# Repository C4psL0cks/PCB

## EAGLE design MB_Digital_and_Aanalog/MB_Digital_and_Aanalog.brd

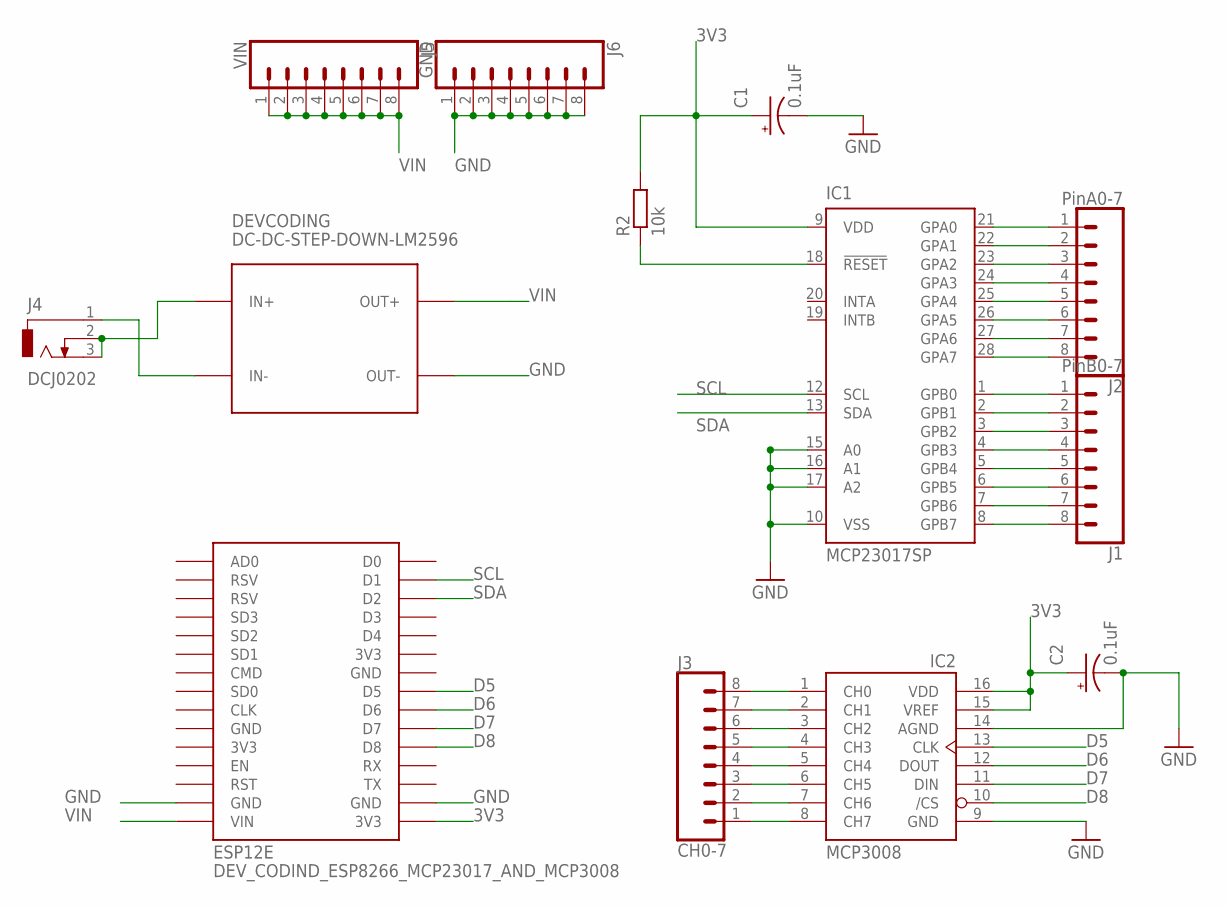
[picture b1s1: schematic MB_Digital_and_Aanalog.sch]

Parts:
C1, C2: 0.1uF; E1,8-4
DEVCODING: DC-DC-STEP-DOWN-LM2596
DEV_CODIND_ESP8266_MCP23017_AND_MCP3008: ESP12E; ESP12E_DEVKIT
IC1: MCP23017SP; DIL28-3
IC2: MCP3008; DIL16
J1: PinB0-7; 1X08_LONGPADS
J2: PinA0-7; 1X08_LONGPADS
J3: CH0-7; 1X08_LONGPADS
J4: DCJ0202
J5: VIN; 1X08_LONGPADS
J6: GND; 1X08_LONGPADS
R2: 10k; 0207/7

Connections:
3V3: C1.+, C2.+, DEV_CODIND_ESP8266_MCP23017_AND_MCP3008.3V3@2 (3V3), IC1.9 (VDD), IC2.15 (VREF), IC2.16 (VDD), R2.2
D5: DEV_CODIND_ESP8266_MCP23017_AND_MCP3008.D5, IC2.13 (CLK)
D6: DEV_CODIND_ESP8266_MCP23017_AND_MCP3008.D6, IC2.12 (DOUT)
D7: DEV_CODIND_ESP8266_MCP23017_AND_MCP3008.D7, IC2.11 (DIN)
D8: DEV_CODIND_ESP8266_MCP23017_AND_MCP3008.D8, IC2.10 (/CS)
GND: C1.-, C2.-, DEVCODING.OUT-, DEV_CODIND_ESP8266_MCP23017_AND_MCP3008.GND@1 (GND), DEV_CODIND_ESP8266_MCP23017_AND_MCP3008.GND@3 (GND), IC1.10 (VSS), IC1.15 (A0), IC1.16 (A1), IC1.17 (A2), IC2.9 (GND), IC2.14 (AGND), J6.1, J6.2, J6.3, J6.4, J6.5, J6.6, J6.7, J6.8
unnamed: IC1.21 (GPA0), J2.1
unnamed: IC1.22 (GPA1), J2.2
unnamed: IC1.23 (GPA2), J2.3
unnamed: IC1.18 (!RESET), R2.1
unnamed: IC1.24 (GPA3), J2.4
unnamed: IC1.25 (GPA4), J2.5
unnamed: IC1.26 (GPA5), J2.6
unnamed: IC1.27 (GPA6), J2.7
unnamed: IC1.28 (GPA7), J2.8
unnamed: IC1.1 (GPB0), J1.1
unnamed: IC1.2 (GPB1), J1.2
unnamed: IC1.3 (GPB2), J1.3
unnamed: IC1.4 (GPB3), J1.4
unnamed: IC1.5 (GPB4), J1.5
unnamed: IC1.6 (GPB5), J1.6
unnamed: IC1.7 (GPB6), J1.7
unnamed: IC1.8 (GPB7), J1.8
unnamed: IC2.1 (CH0), J3.8
unnamed: IC2.2 (CH1), J3.7
unnamed: IC2.3 (CH2), J3.6
unnamed: IC2.4 (CH3), J3.5
unnamed: IC2.5 (CH4), J3.4
unnamed: IC2.6 (CH5), J3.3
unnamed: IC2.7 (CH6), J3.2
unnamed: IC2.8 (CH7), J3.1
unnamed: DEVCODING.IN-, J4.1
unnamed: DEVCODING.IN+, J4.2, J4.3
SCL: DEV_CODIND_ESP8266_MCP23017_AND_MCP3008.D1, IC1.12 (SCL)
SDA: DEV_CODIND_ESP8266_MCP23017_AND_MCP3008.D2, IC1.13 (SDA)
VIN: DEVCODING.OUT+, DEV_CODIND_ESP8266_MCP23017_AND_MCP3008.VIN, J5.1, J5.2, J5.3, J5.4, J5.5, J5.6, J5.7, J5.8

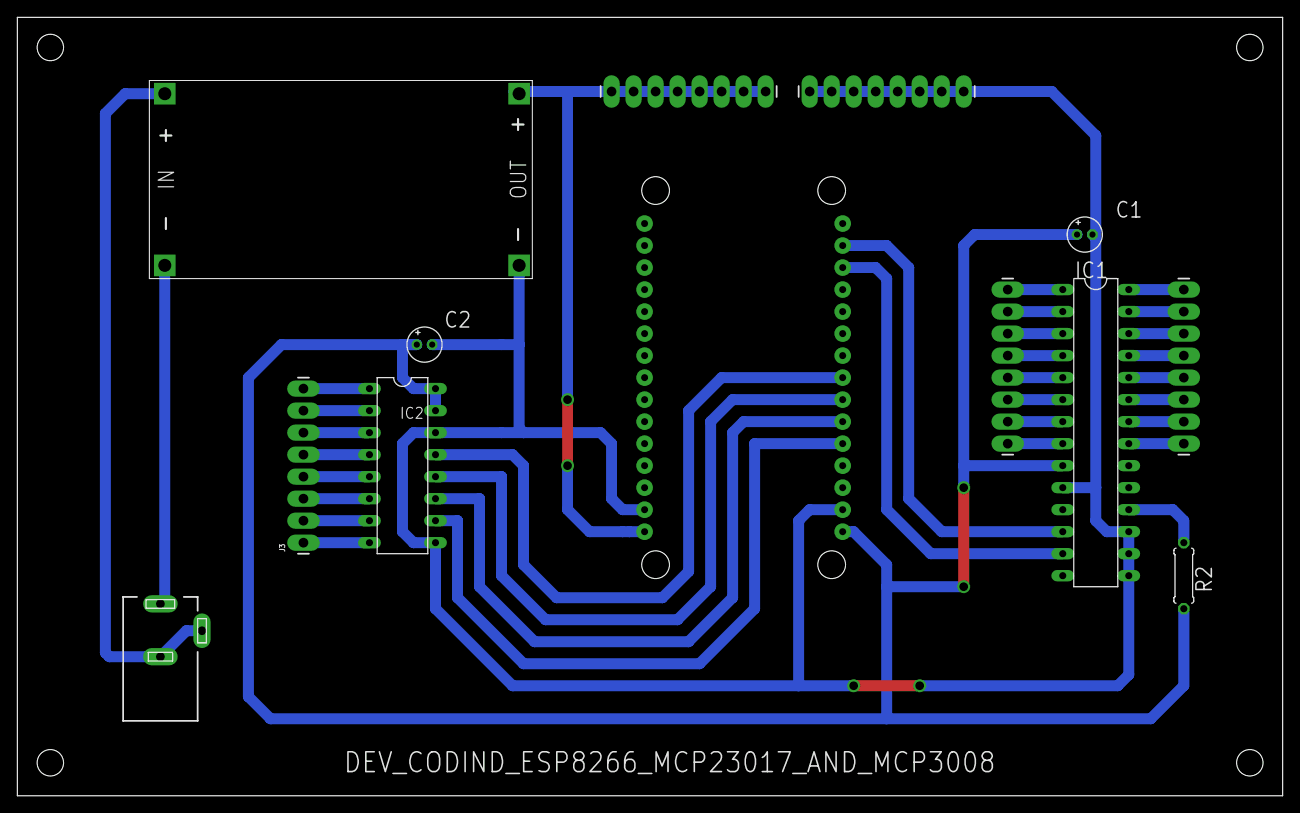
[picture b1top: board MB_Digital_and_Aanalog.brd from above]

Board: 2 copper layers, 146.0 x 89.8 mm, 13 parts (0 on the bottom side), 36 nets.

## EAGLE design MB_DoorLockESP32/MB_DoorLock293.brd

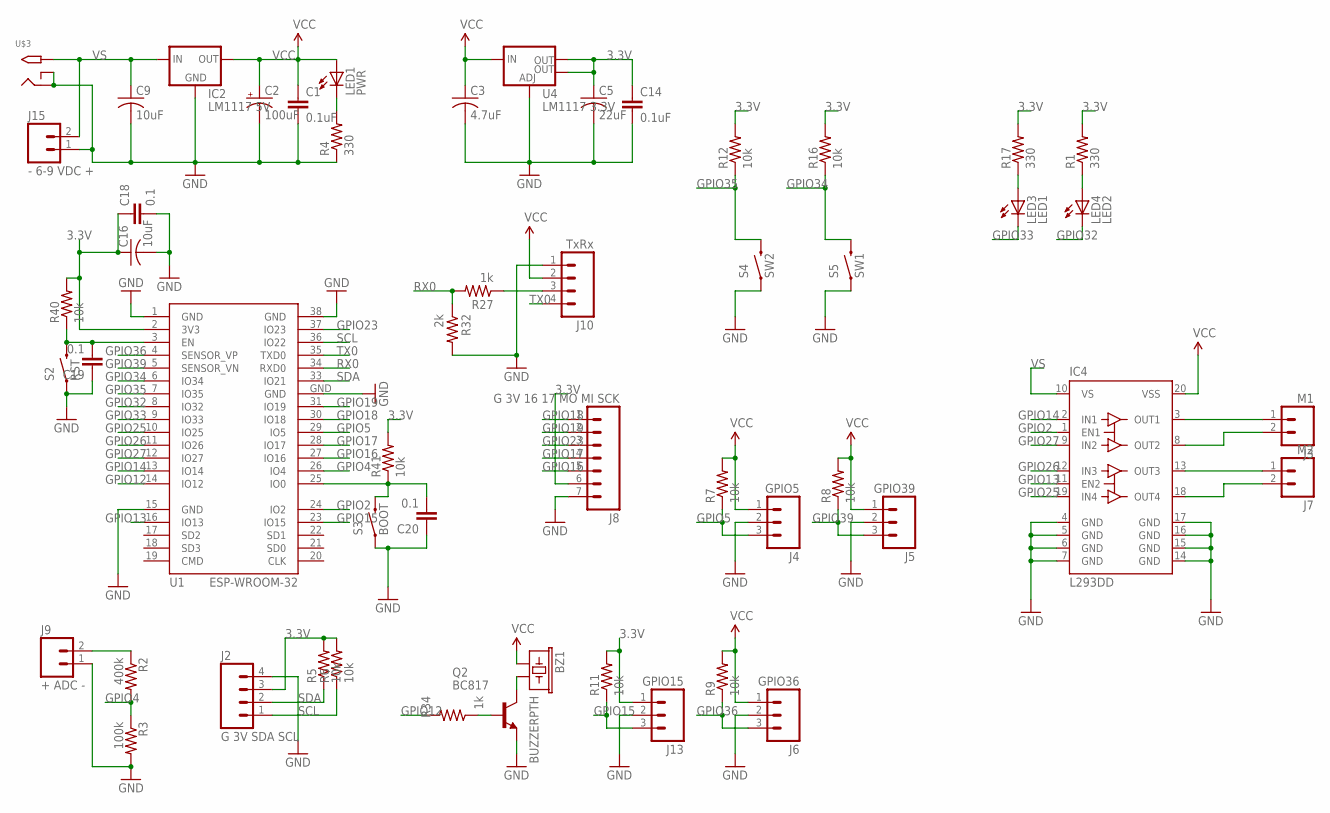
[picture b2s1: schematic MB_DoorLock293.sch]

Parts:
BZ1: BUZZERPTH; BUZZER-12MM
C1, C14: 0.1uF; 0805
C2: 100uF; EIA3528-KIT
C3: 4.7uF; C1206
C5: 22uF; C1206
C9, C16: 10uF; C1206
C18, C19, C20: 0.1; 0805
IC2: LM1117 5V; TO252
IC4: L293DD; SO20
J2: G 3V SDA SCL; JST-4-PTH-VERT
J3: M1; JST-2-PTH-VERT
J4: GPIO5; JST-3-PTH-VERT
J5: GPIO39; JST-3-PTH-VERT
J6: GPIO36; JST-3-PTH-VERT
J7: M2; JST-2-PTH-VERT
J8: G 3V 16 17 MO MI SCK; 1X07
J9: + ADC -; JST-2-PTH-VERT
J10: TxRx; MOLEX-1X4
J13: GPIO15; JST-3-PTH-VERT
J15: - 6-9 VDC +; JST-2-PTH-VERT
LED1: PWR; CHIP-LED0805
LED3: LED1; CHIP-LED0805
LED4: LED2; CHIP-LED0805
Q2: BC817; SOT23-BEC
R1, R4, R17: 330; 0805
R2: 400k; 0805
R3: 100k; 0805
R5, R6, R7, R8, R9, R11, R12, R16, R40, R41: 10k; 0805
R27, R34: 1k; 0805
R32: 2k; 0805
S2: RST; TACTILE-SWITCH-1101NE
S3: BOOT; TACTILE-SWITCH-1101NE
S4: SW2; TACTILE-SWITCH-1101NE
S5: SW1; TACTILE-SWITCH-1101NE
U1: ESP-WROOM-32
U4: LM1117 3.3V; SOT223
U$3: 7*12V; PJ-102A

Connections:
3.3V: C5.1, C14.1, C16.1, C18.1, J2.3, J8.6, J13.1, R1.2, R5.2, R6.2, R11.2, R12.2, R16.2, R17.2, R40.2, R41.2, U1.2 (3V3), U4.2 (OUT), U4.4 (OUT)
GND: C1.2, C2.C (-), C3.2, C5.2, C9.2, C14.2, C16.2, C18.2, C19.1, C20.1, IC2.1 (GND), IC4.4 (GND), IC4.5 (GND), IC4.6 (GND), IC4.7 (GND), IC4.14 (GND), IC4.15 (GND), IC4.16 (GND), IC4.17 (GND), J2.4, J4.2, J5.2, J6.2, J8.7, J9.1, J10.1, J13.2, J15.1, Q2.E, R3.2, R4.1, R32.2, S2.1, S3.1, S4.1, S5.1, U1.1 (GND), U1.15 (GND), U1.38 (GND), U1.GND, U4.1 (ADJ), U$3.RING, U$3.RING_SW
GPIO2: IC4.1 (EN1), U1.24 (IO2)
GPIO4: R2.2, R3.1, U1.26 (IO4)
GPIO5: J4.3, R7.1, U1.29 (IO5)
GPIO12: R34.2, U1.14 (IO12)
GPIO13: IC4.11 (EN2), U1.16 (IO13)
GPIO14: IC4.2 (IN1), U1.13 (IO14)
GPIO15: J13.3, R11.1, U1.23 (IO15)
GPIO16: J8.5, U1.27 (IO16)
GPIO17: J8.4, U1.28 (IO17)
GPIO18: J8.1, U1.30 (IO18)
GPIO19: J8.2, U1.31 (IO19)
GPIO23: J8.3, U1.37 (IO23)
GPIO25: IC4.19 (IN4), U1.10 (IO25)
GPIO26: IC4.12 (IN3), U1.11 (IO26)
GPIO27: IC4.9 (IN2), U1.12 (IO27)
GPIO32: LED4.C, U1.8 (IO32)
GPIO33: LED3.C, U1.9 (IO33)
GPIO34: R16.1, S5.2, U1.6 (IO34)
GPIO35: R12.1, S4.2, U1.7 (IO35)
GPIO36: J6.3, R9.1, U1.4 (SENSOR_VP)
GPIO39: J5.3, R8.1, U1.5 (SENSOR_VN)
unnamed: IC4.3 (OUT1), J3.1
unnamed: IC4.13 (OUT3), J7.1
unnamed: J9.2, R2.1
unnamed: J10.3, R27.1
unnamed: LED3.A, R17.1
unnamed: C20.2, R41.1, S3.2, U1.25 (IO0)
unnamed: LED1.C, R4.2
unnamed: LED4.A, R1.1
unnamed: IC4.8 (OUT2), J3.2
unnamed: C19.2, R40.1, S2.2, U1.3 (EN)
unnamed: IC4.18 (OUT4), J7.2
unnamed: Q2.B, R34.1
unnamed: BZ1.- (2), Q2.C
RX0: R27.2, R32.1, U1.34 (RXD0)
SCL: J2.1, R6.1, U1.36 (IO22)
SDA: J2.2, R5.1, U1.33 (IO21)
TX0: J10.4, U1.35 (TXD0)
VCC: BZ1.+ (1), C1.1, C2.A (+), C3.1, IC2.TAB (OUT), IC4.20 (VSS), J4.1, J5.1, J6.1, J10.2, LED1.A, R7.2, R8.2, R9.2, U4.3 (IN)
VS: C9.1, IC2.2 (IN), IC4.10 (VS), J15.2, U$3.TIP

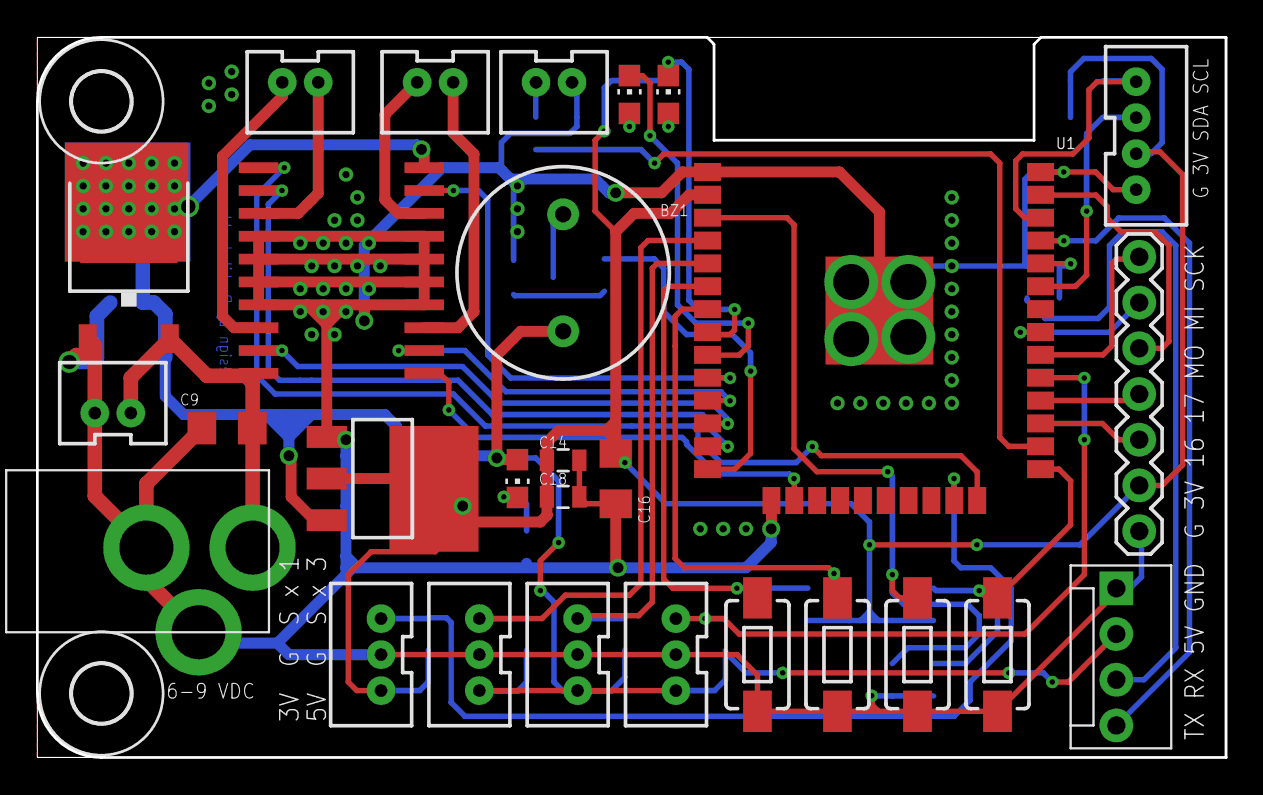
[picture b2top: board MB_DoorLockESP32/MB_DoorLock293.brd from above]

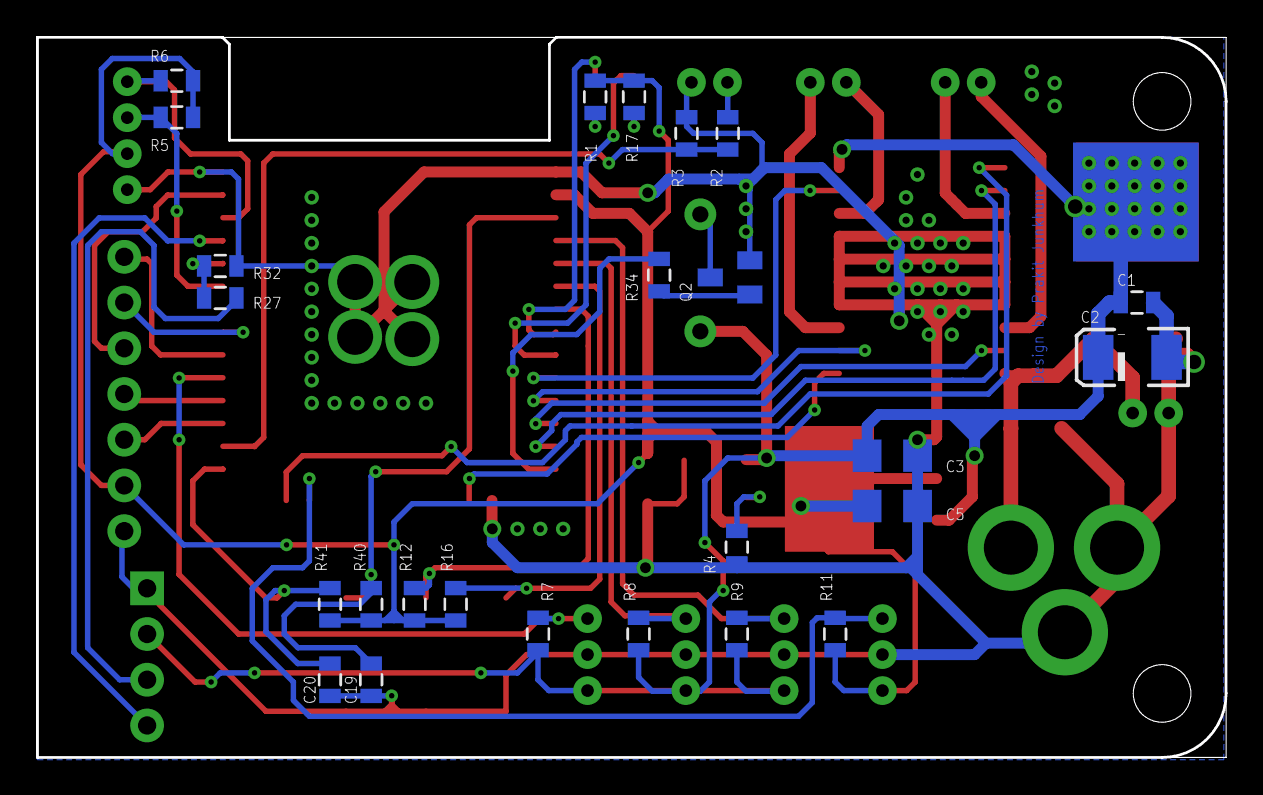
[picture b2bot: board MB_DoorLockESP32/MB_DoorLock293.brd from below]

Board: 2 copper layers, 66.0 x 40.0 mm, 55 parts (25 on the bottom side), 42 nets.

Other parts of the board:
U$1, U$2: 3,2

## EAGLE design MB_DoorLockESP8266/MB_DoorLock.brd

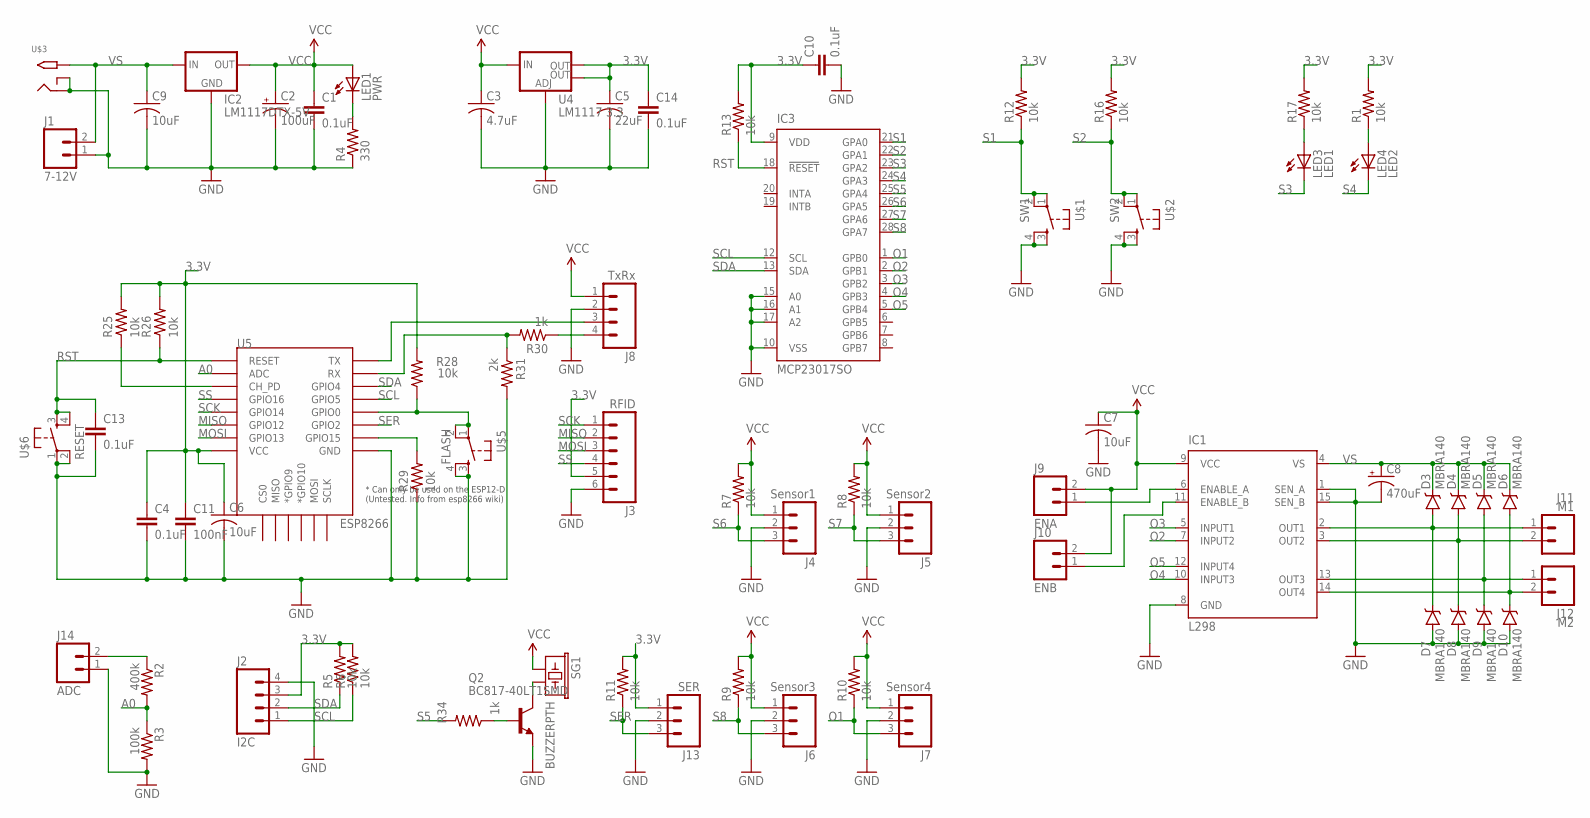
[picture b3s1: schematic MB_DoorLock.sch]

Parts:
C1, C4, C10, C13, C14: 0.1uF; 0805
C2: 100uF; EIA3528-KIT
C3: 4.7uF; C1206
C5: 22uF; C1206
C6, C7, C9: 10uF; C1206
C8: 470uF; 153CLV-1012
C11: 100nF; 0805
D3, D4, D5, D6, D7, D8, D9, D10: MBRA140; SMA-DIODE
IC1: L298; MULTIWATT-15
IC2: LM1117DTX-5V; TO252
IC3: MCP23017SO; SO28W
J1: 7-12V; MOLEX-1X2
J2: I2C; JST-4-PTH-VERT
J3: RFID; MOLEX-1X6
J4: Sensor1; JST-3-PTH-VERT
J5: Sensor2; JST-3-PTH-VERT
J6: Sensor3; JST-3-PTH-VERT
J7: Sensor4; JST-3-PTH-VERT
J8: TxRx; MOLEX-1X4
J9: ENA; 1X02
J10: ENB; 1X02
J11: M1; MOLEX-1X2
J12: M2; MOLEX-1X2
J13: SER; JST-3-PTH-VERT
J14: ADC; MOLEX-1X2
LED1: PWR; CHIP-LED0805
LED3: LED1; CHIP-LED0805
LED4: LED2; CHIP-LED0805
Q2: BC817-40LT1SMD; SOT23-BEC
R1, R5, R6, R7, R8, R9, R10, R11, R12, R13, R16, R17, R25, R26, R28, R29: 10k; 0805
R2: 400k; 0805
R3: 100k; 0805
R4: 330; 0805
R30, R34: 1k; 0805
R31: 2k; 0805
SG1: BUZZERPTH; BUZZER-12MM
U4: LM1117 3.3; SOT223
U5: ESP8266; ESP12E-SMD
U$1: SW1; TAC-SWITCH-PTH
U$2: SW2; TAC-SWITCH-PTH
U$3: 7*12V; PJ-102A
U$5: FLASH; TAC-SWITCH-PTH
U$6: RESET; TAC-SWITCH-PTH

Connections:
3.3V: C4.1, C5.1, C6.1, C10.1, C11.1, C14.1, IC3.9 (VDD), J2.3, J3.5, J13.1, R1.2, R5.2, R6.2, R11.2, R12.2, R13.2, R16.2, R17.2, R25.2, R26.2, R28.2, U4.2 (OUT), U4.4 (OUT), U5.VCC
A0: R2.2, R3.1, U5.ADC
GND: C1.2, C2.C (-), C3.2, C4.2, C5.2, C6.2, C7.2, C8.-, C9.2, C10.2, C11.2, C13.2, C14.2, D7.A, D8.A, D9.A, D10.A, IC1.1 (SEN_A), IC1.8 (GND), IC1.15 (SEN_B), IC2.1 (GND), IC3.10 (VSS), IC3.15 (A0), IC3.16 (A1), IC3.17 (A2), J1.1, J2.4, J3.6, J4.2, J5.2, J6.2, J7.2, J8.2, J13.2, J14.1, Q2.E, R3.2, R4.1, R29.1, R31.2, U4.1 (ADJ), U5.GND, U$1.3, U$1.4, U$2.3, U$2.4, U$3.RING, U$3.RING_SW, U$5.3, U$5.4, U$6.1, U$6.2
MISO: J3.2, U5.GPIO12
MOSI: J3.3, U5.GPIO13
unnamed: IC1.6 (ENABLE_A), J9.1
unnamed: IC1.11 (ENABLE_B), J10.1
unnamed: J14.2, R2.1
unnamed: LED3.A, R17.1
unnamed: D3.A, D7.C, IC1.2 (OUT1), J11.1
unnamed: D4.A, D8.C, IC1.3 (OUT2), J11.2
unnamed: D5.A, D9.C, IC1.13 (OUT3), J12.1
unnamed: LED1.C, R4.2
unnamed: D6.A, D10.C, IC1.14 (OUT4), J12.2
unnamed: LED4.A, R1.1
unnamed: J8.4, R30.1
unnamed: R30.2, R31.1, U5.RXD0 (RX)
unnamed: Q2.B, R34.1
unnamed: R25.1, U5.CH_PD
unnamed: R28.1, U5.GPIO0, U$5.1, U$5.2
unnamed: R29.2, U5.GPIO15
unnamed: Q2.C, SG1.- (2)
unnamed: J8.3, U5.TXD0 (TX)
O1: IC3.1 (GPB0), J7.3, R10.1
O2: IC1.7 (INPUT2), IC3.2 (GPB1)
O3: IC1.5 (INPUT1), IC3.3 (GPB2)
O4: IC1.10 (INPUT3), IC3.4 (GPB3)
O5: IC1.12 (INPUT4), IC3.5 (GPB4)
RST: C13.1, IC3.18 (!RESET), R13.1, R26.1, U5.RESET, U$6.3, U$6.4
S1: IC3.21 (GPA0), R12.1, U$1.1, U$1.2
S2: IC3.22 (GPA1), R16.1, U$2.1, U$2.2
S3: IC3.23 (GPA2), LED3.C
S4: IC3.24 (GPA3), LED4.C
S5: IC3.25 (GPA4), R34.2
S6: IC3.26 (GPA5), J4.3, R7.1
S7: IC3.27 (GPA6), J5.3, R8.1
S8: IC3.28 (GPA7), J6.3, R9.1
SCK: J3.1, U5.GPIO14
SCL: IC3.12 (SCL), J2.1, R6.1, U5.GPIO5
SDA: IC3.13 (SDA), J2.2, R5.1, U5.GPIO4
SER: J13.3, R11.1, U5.GPIO2
SS: J3.4, U5.GPIO16
VCC: C1.1, C2.A (+), C3.1, C7.1, IC1.9 (VCC), IC2.TAB (OUT), J4.1, J5.1, J6.1, J7.1, J8.1, J9.2, J10.2, LED1.A, R7.2, R8.2, R9.2, R10.2, SG1.+ (1), U4.3 (IN)
VS: C8.+, C9.1, D3.C, D4.C, D5.C, D6.C, IC1.4 (VS), IC2.2 (IN), J1.2, U$3.TIP

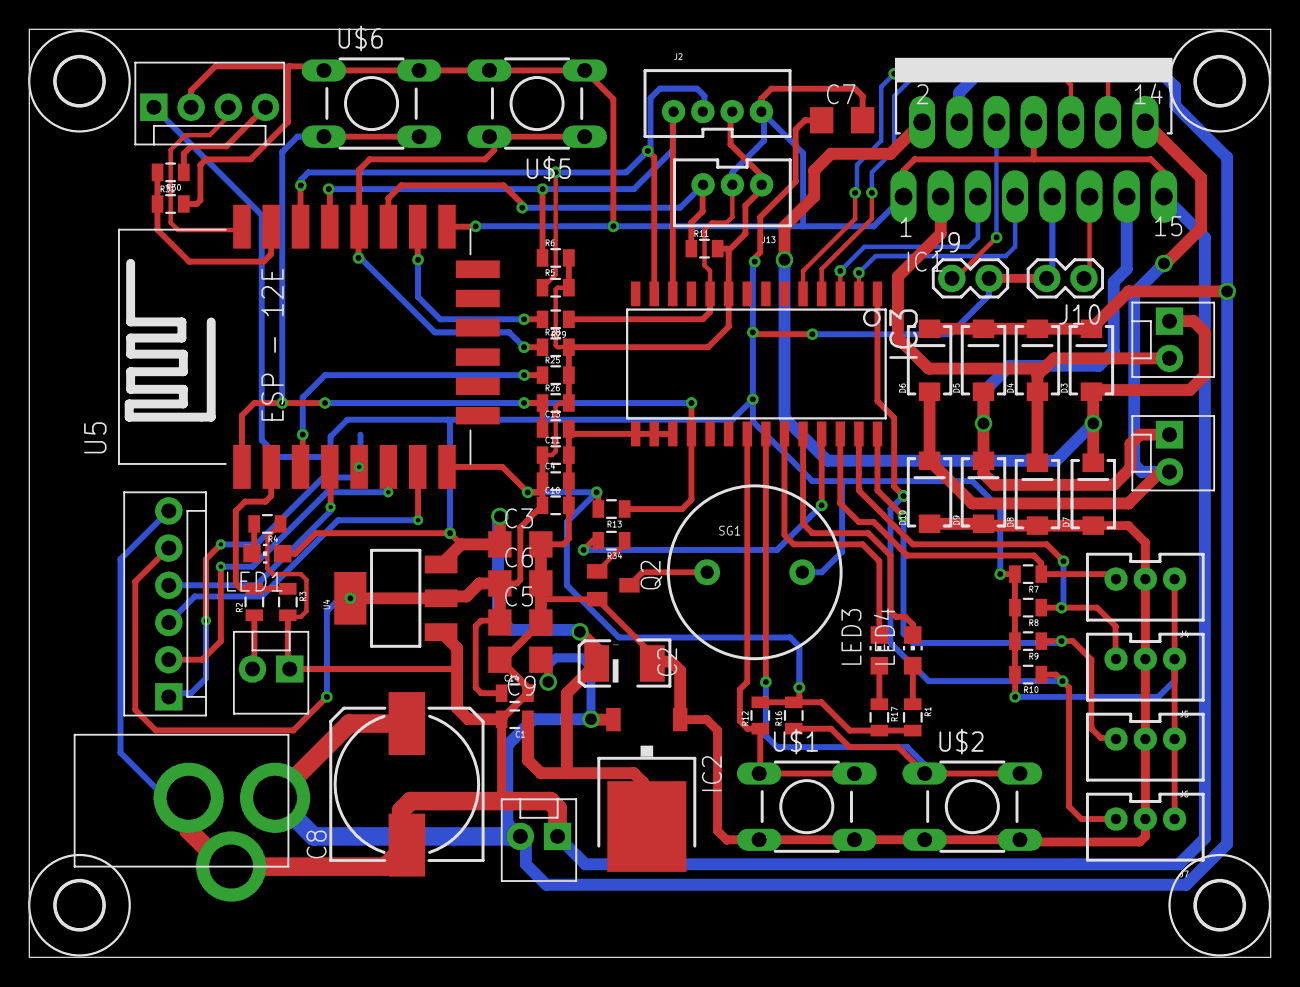
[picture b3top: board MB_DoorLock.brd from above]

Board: 2 copper layers, 84.8 x 63.4 mm, 76 parts (0 on the bottom side), 44 nets.

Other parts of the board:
U$4, U$7, U$8, U$9: 3,2

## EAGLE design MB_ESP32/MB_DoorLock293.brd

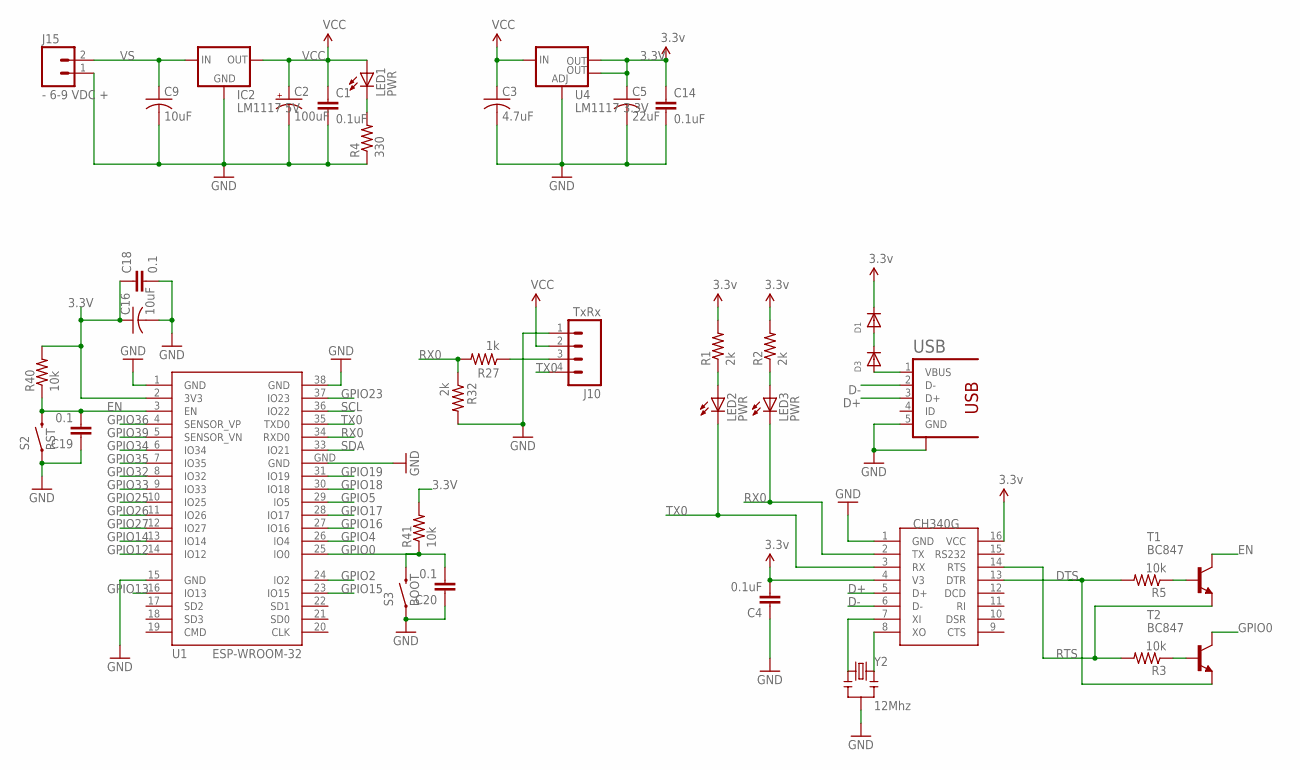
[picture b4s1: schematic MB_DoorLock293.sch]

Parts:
C1, C4, C14: 0.1uF; 0805
C2: 100uF; EIA3528-KIT
C3: 4.7uF; C1206
C5: 22uF; C1206
C9, C16: 10uF; C1206
C18, C19, C20: 0.1; 0805
D1, D3: DIODESOD-323F; SOD-323F
IC2: LM1117 5V; TO252
J10: TxRx; MOLEX-1X4
J15: - 6-9 VDC +; JST-2-PTH-VERT
LED1, LED2, LED3: PWR; CHIP-LED0805
R1, R2, R32: 2k; 0805
R3, R5, R40, R41: 10k; 0805
R4: 330; 0805
R27: 1k; 0805
S2: RST; TACTILE-SWITCH-1101NE
S3: BOOT; TACTILE-SWITCH-1101NE
T1, T2: BC847; SOT23
U1: ESP-WROOM-32
U4: LM1117 3.3V; SOT223
U$1: CH340G; SOIC16
USB: 1981584-1
Y2: 12Mhz; RESONATOR-SMD

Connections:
3.3V: C5.1, C14.1, C16.1, C18.1, R40.2, R41.2, U1.2 (3V3), U4.2 (OUT), U4.4 (OUT)
D+: U$1.5 (D+), USB.3 (D+)
D-: U$1.6 (D-), USB.2 (D-)
DTS: R5.2, T2.2 (E), U$1.13 (DTR)
EN: C19.2, R40.1, S2.2, T1.3 (C), U1.3 (EN)
GND: C1.2, C2.C (-), C3.2, C4.1, C5.2, C9.2, C14.2, C16.2, C18.2, C19.1, C20.1, IC2.1 (GND), J10.1, J15.1, R4.1, R32.2, S2.1, S3.1, U1.1 (GND), U1.15 (GND), U1.38 (GND), U1.GND, U4.1 (ADJ), U$1.1 (GND), USB.5 (GND), USB.S1, Y2.2
GPIO0: C20.2, R41.1, S3.2, T2.3 (C), U1.25 (IO0)
GPIO2: U1.24 (IO2)
GPIO4: U1.26 (IO4)
GPIO5: U1.29 (IO5)
GPIO12: U1.14 (IO12)
GPIO13: U1.16 (IO13)
GPIO14: U1.13 (IO14)
GPIO15: U1.23 (IO15)
GPIO16: U1.27 (IO16)
GPIO17: U1.28 (IO17)
GPIO18: U1.30 (IO18)
GPIO19: U1.31 (IO19)
GPIO23: U1.37 (IO23)
GPIO25: U1.10 (IO25)
GPIO26: U1.11 (IO26)
GPIO27: U1.12 (IO27)
GPIO32: U1.8 (IO32)
GPIO33: U1.9 (IO33)
GPIO34: U1.6 (IO34)
GPIO35: U1.7 (IO35)
GPIO36: U1.4 (SENSOR_VP)
GPIO39: U1.5 (SENSOR_VN)
unnamed: LED2.A, R1.1
unnamed: LED3.A, R2.1
unnamed: D3.A, USB.1 (VBUS)
unnamed: J10.3, R27.1
unnamed: D1.A, D3.C
unnamed: U$1.7 (XI), Y2.1
unnamed: R5.1, T1.1 (B)
unnamed: R3.1, T2.1 (B)
unnamed: LED1.C, R4.2
unnamed: U$1.8 (XO), Y2.3
RTS: R3.2, T1.2 (E), U$1.14 (RTS)
RX0: LED3.C, R27.2, R32.1, U1.34 (RXD0), U$1.2 (TX)
SCL: U1.36 (IO22)
SDA: U1.33 (IO21)
TX0: J10.4, LED2.C, U1.35 (TXD0), U$1.3 (RX)
VCC: C1.1, C2.A (+), C3.1, C4.2, D1.C, IC2.TAB (OUT), J10.2, LED1.A, R1.2, R2.2, U4.3 (IN), U$1.4 (V3), U$1.16 (VCC)
VS: C9.1, IC2.2 (IN), J15.2

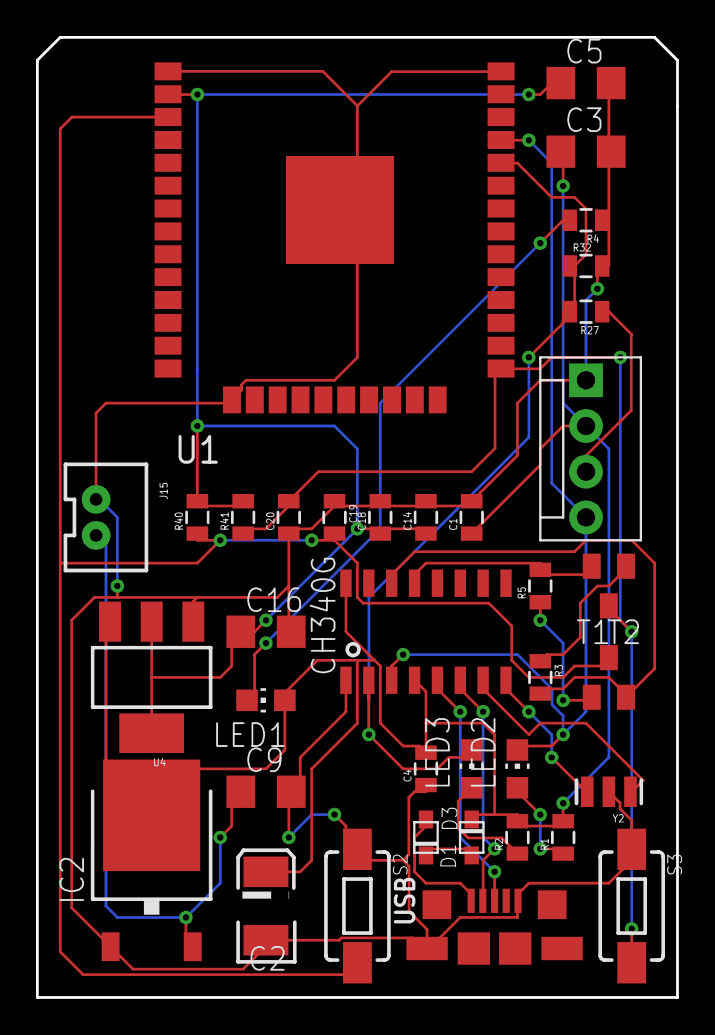
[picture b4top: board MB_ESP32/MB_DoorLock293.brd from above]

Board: 2 copper layers, 35.6 x 53.3 mm, 37 parts (0 on the bottom side), 22 nets.

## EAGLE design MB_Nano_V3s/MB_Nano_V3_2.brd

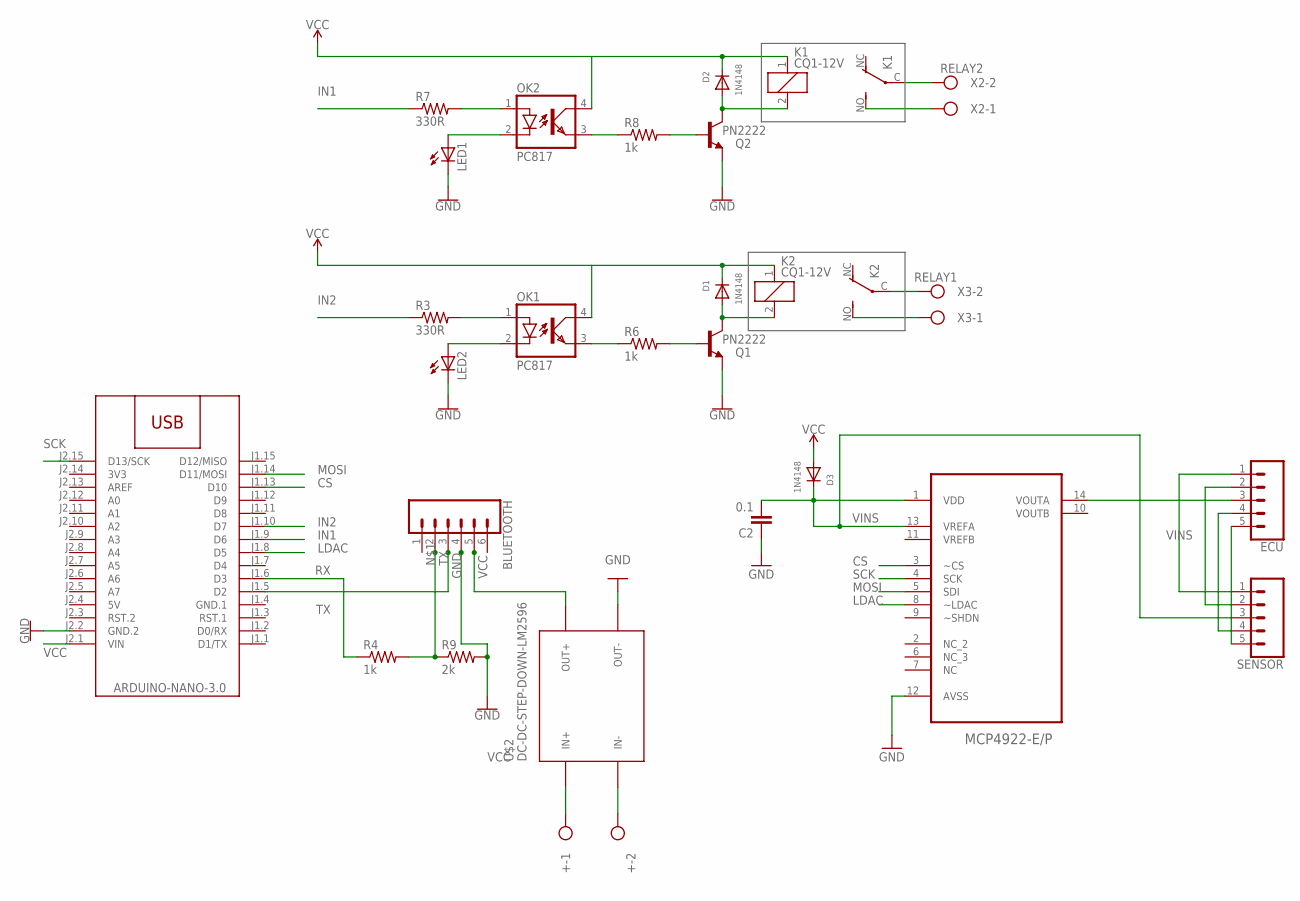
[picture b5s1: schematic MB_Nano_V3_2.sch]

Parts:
+: Vcc; W237-102
BLUETOOTH: CONN_06LONGPADS; 1X06_LONGPADS
C2: 0.1; CAP-PTH-5MM
D1, D2, D3: 1N4148; DO-1N4148
ECU: CONN_05PTH_LONGPADS; 1X05_LONGPADS
K1, K2: CQ1-12V; CQ1
LED1, LED2: LED3MM
M2: ARDUINO-NANO-3.0
OK1, OK2: PC817; DIL04
Q1, Q2: PN2222; TO92-EBC
R3, R7: 330R; 0204/7
R4, R6, R8: 1k; 0204/7
R9: 2k; 0204/7
SENSOR: CONN_05PTH_LONGPADS; 1X05_LONGPADS
U$2: DC-DC-STEP-DOWN-LM2596
U$3: MCP4922-E/P; DIP254P762X533-14
X2: RELAY2; W237-102
X3: RELAY1; W237-102

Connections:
1: ECU.5, SENSOR.5
2: ECU.4, SENSOR.4
3V3: M2.J2.14 (3V3)
4: ECU.2, SENSOR.2
5: ECU.1, SENSOR.1
5V: M2.J2.4 (5V)
22: D2.A, K1.2, Q2.C
+: +.1, U$2.IN+
-: +.2, U$2.IN-
CS: M2.J1.13 (D10), U$3.3 (~CS)
GND: BLUETOOTH.4, C2.1, LED1.K (C), LED2.K (C), M2.J2.2 (GND.2), Q1.E, Q2.E, R9.2, U$2.OUT-, U$3.12 (AVSS)
GND-: D1.A, K2.2, Q1.C
GND.1: M2.J1.4 (GND.1)
IN1: M2.J1.9 (D6), R7.1
IN2: M2.J1.10 (D7), R3.1
INS: OK1.1 (A), R3.2
INSS: OK2.1 (A), R7.2
LDAC: M2.J1.8 (D5), U$3.8 (~LDAC)
LED: LED2.A, OK1.2 (C)
LEDS: LED1.A, OK2.2 (C)
MOSI: M2.J1.14 (D11/MOSI), U$3.5 (SDI)
unnamed: BLUETOOTH.2, R4.2, R9.1
unnamed: K1.NO (S), X2.1
unnamed: K1.C, X2.2
unnamed: K2.NO (S), X3.1
unnamed: K2.C, X3.2
unnamed: Q1.B, R6.2
unnamed: Q2.B, R8.2
unnamed: OK2.3 (EMIT), R8.1
OTP: OK1.3 (EMIT), R6.1
RX: M2.J1.6 (D3), R4.1
SCK: M2.J2.15 (D13/SCK), U$3.4 (SCK)
TX: BLUETOOTH.3, M2.J1.5 (D2)
VCC: BLUETOOTH.5, D1.C, D2.C, D3.A, K1.1, K2.1, M2.J2.1 (VIN), OK1.4 (COL), OK2.4 (COL), U$2.OUT+
VINS: C2.2, D3.C, SENSOR.3, U$3.1 (VDD), U$3.13 (VREFA)
VOUT: ECU.3, U$3.14 (VOUTA)

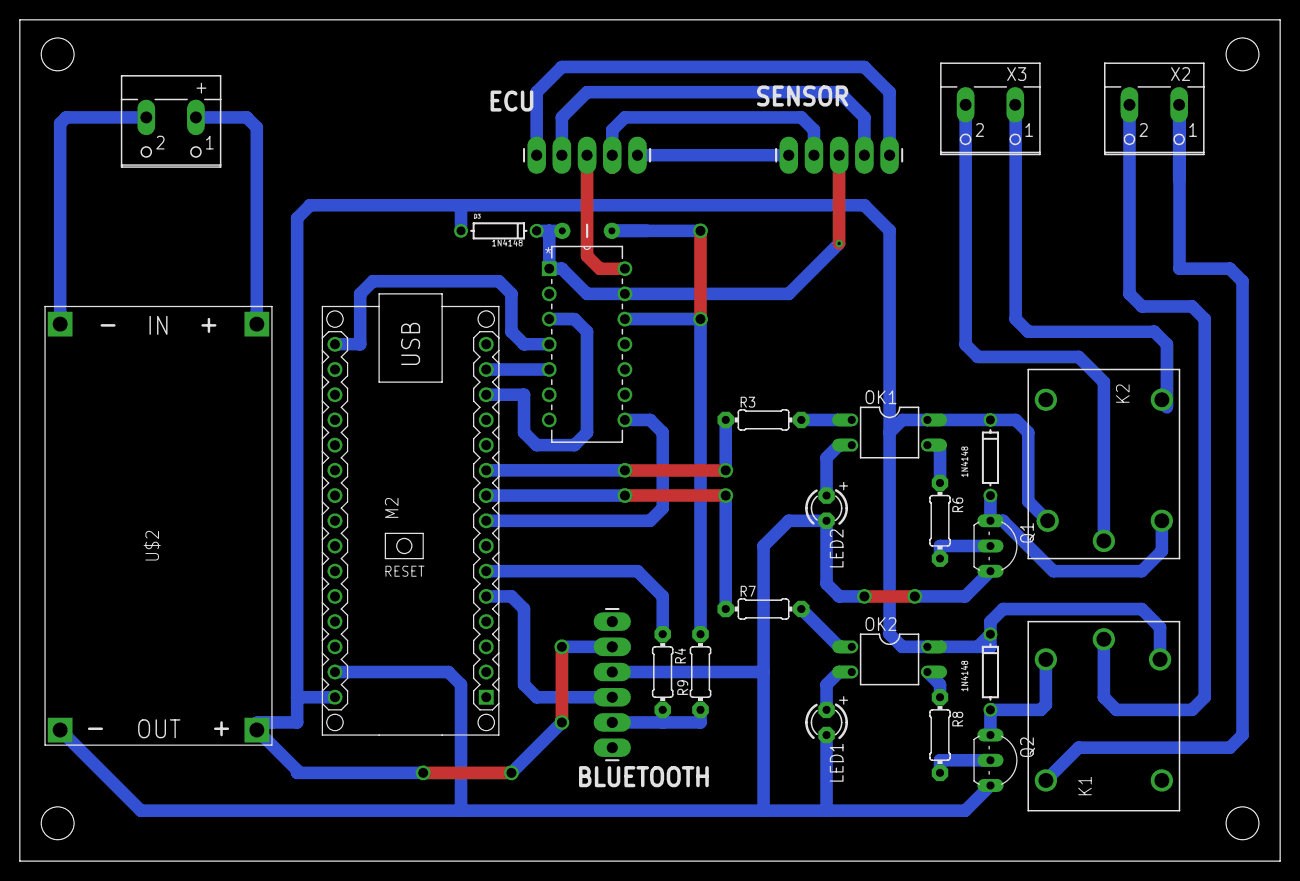
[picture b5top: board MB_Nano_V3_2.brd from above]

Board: 2 copper layers, 127.0 x 84.8 mm, 27 parts (0 on the bottom side), 33 nets.

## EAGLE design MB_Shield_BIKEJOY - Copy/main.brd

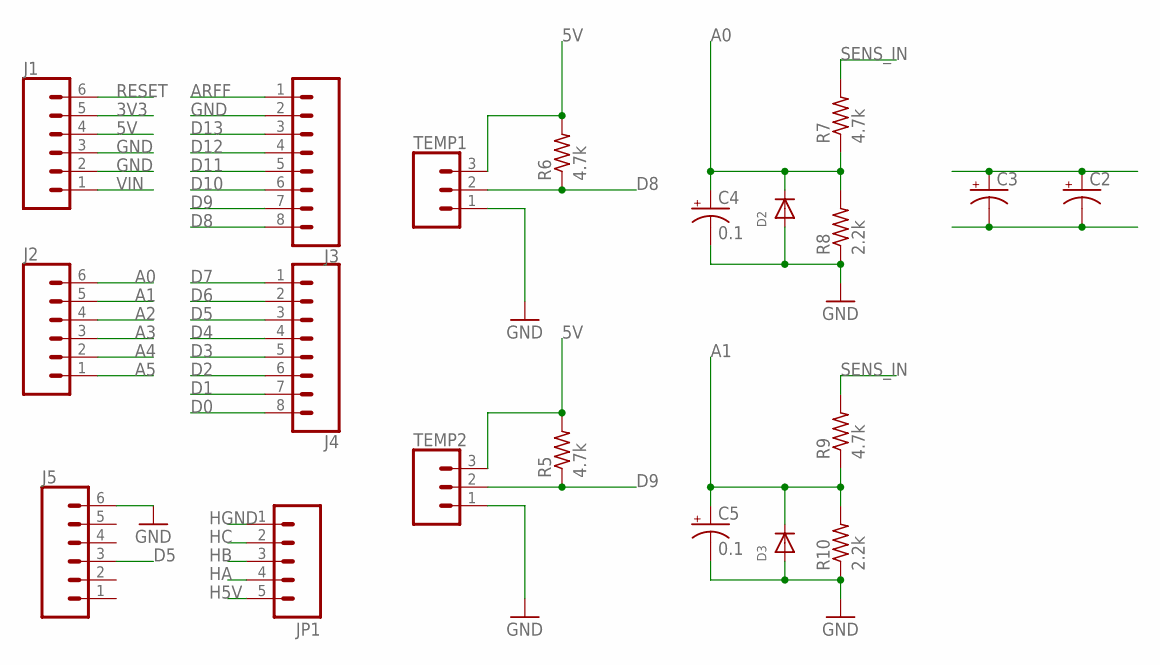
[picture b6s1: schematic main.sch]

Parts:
C2, C3: C-POL-US_RADIAL-32MM-DIA; CAPPRD1000W100D2275H3200B
C4, C5: 0.1; B45181A
D2, D3: DIODEDO-1N4148; DO-1N4148
J1, J2, J5: CONN_06NO_SILK_FEMALE_PTH; 1X06_NO_SILK
J3, J4: CONN_08NO_SILK_FEMALE_PTH; 1X08_NO_SILK
JP1: M05PTH; 1X05
R5, R6, R7, R9: 4.7k; 0207/7
R8, R10: 2.2k; 0207/7
TEMP1, TEMP2: CONN_03; 1X03

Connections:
3V3: J1.5
5V: J1.4, R5.2, R6.2, TEMP1.3, TEMP2.3
A0: C4.+, D2.C, J2.6, R7.1, R8.2
A1: C5.+, D3.C, J2.5, R9.1, R10.2
A2: J2.4
A3: J2.3
A4: J2.2
A5: J2.1
ARFF: J3.1
D0: J4.8
D1: J4.7
D2: J4.6
D3: J4.5
D4: J4.4
D5: J4.3, J5.3
D6: J4.2
D7: J4.1
D8: J3.8, R6.1, TEMP1.2
D9: J3.7, R5.1, TEMP2.2
D10: J3.6
D11: J3.5
D12: J3.4
D13: J3.3
GND: C4.-, C5.-, D2.A, D3.A, J1.2, J1.3, J3.2, J5.6, R8.1, R10.1, TEMP1.1, TEMP2.1
H5V: JP1.5
HA: JP1.4
HB: JP1.3
HC: JP1.2
HGND: JP1.1
unnamed: C2.1 (+), C3.1 (+)
unnamed: C2.2 (-), C3.2 (-)
RESET: J1.6
SENS_IN: R7.2, R9.2
VIN: J1.1

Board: 2 copper layers, 20 parts (0 on the bottom side), 10 nets, no tracks yet.

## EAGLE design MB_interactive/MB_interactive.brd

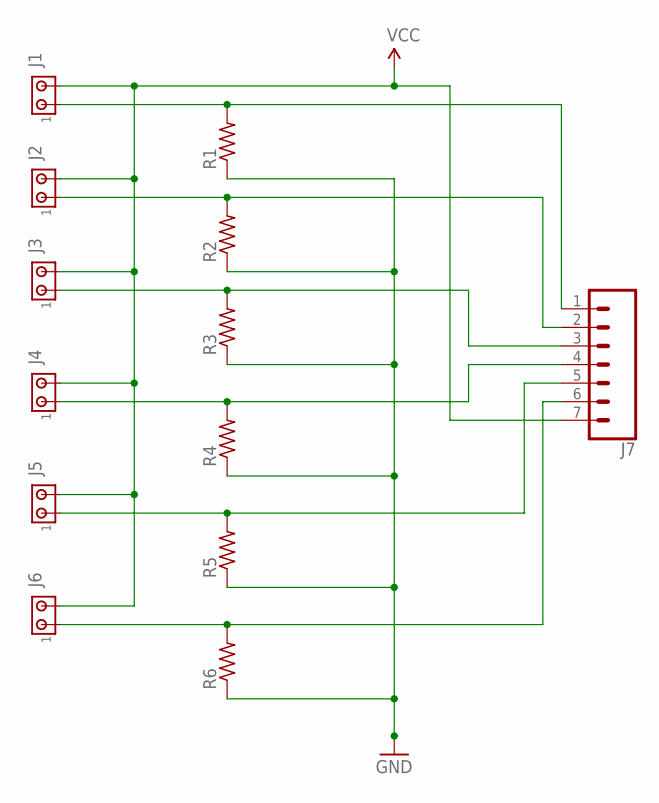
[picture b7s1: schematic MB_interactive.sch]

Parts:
J1, J2, J3, J4, J5, J6: MTA02-100; 10X02MTA
J7: CONN_07; 1X07
R1, R2, R3, R4, R5, R6: R-US_0207/7; 0207/7

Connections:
GND: R1.1, R2.1, R3.1, R4.1, R5.1, R6.1
unnamed: J1.1, J7.1, R1.2
unnamed: J2.1, J7.2, R2.2
unnamed: J3.1, J7.3, R3.2
unnamed: J4.1, J7.4, R4.2
unnamed: J5.1, J7.5, R5.2
unnamed: J6.1, J7.6, R6.2
VCC: J1.2, J2.2, J3.2, J4.2, J5.2, J6.2, J7.7

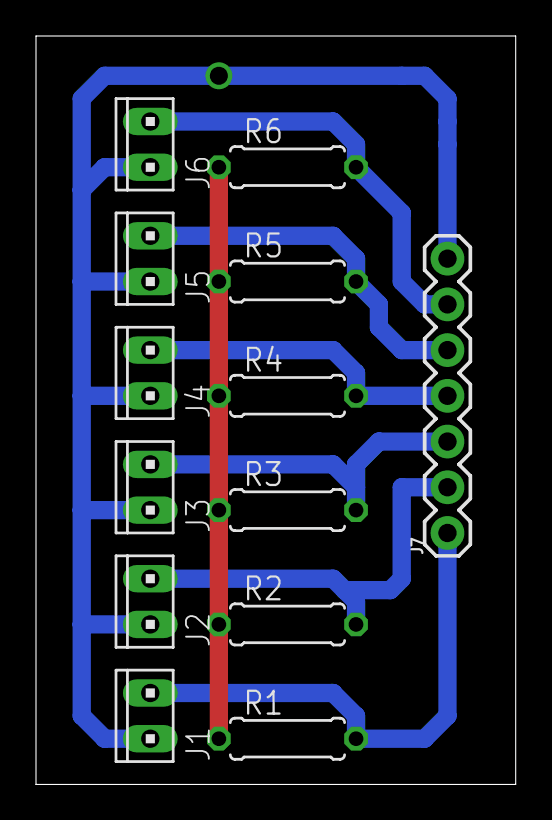
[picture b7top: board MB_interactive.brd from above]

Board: 2 copper layers, 26.6 x 41.6 mm, 13 parts (0 on the bottom side), 8 nets.

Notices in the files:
parts and their libraries:
SparkFun-Connectors: Licensing: Creative Commons ShareAlike 4.0 International - https://creativecommons.org/licenses/by-sa/4.0
diy-modules: Released under the Creative Commons Attribution 4.0 International License: http://creativecommons.org/licenses/by/4.0
